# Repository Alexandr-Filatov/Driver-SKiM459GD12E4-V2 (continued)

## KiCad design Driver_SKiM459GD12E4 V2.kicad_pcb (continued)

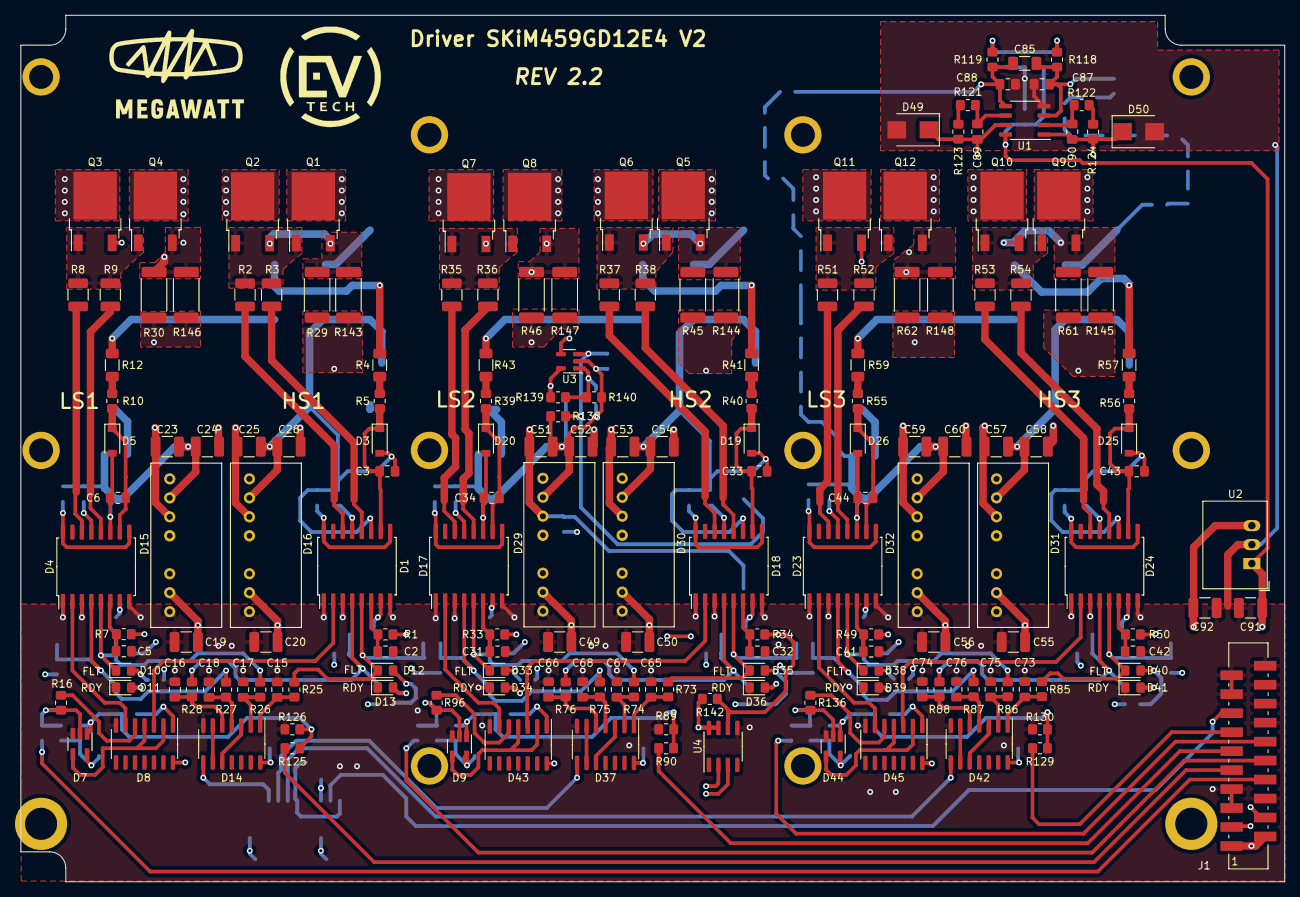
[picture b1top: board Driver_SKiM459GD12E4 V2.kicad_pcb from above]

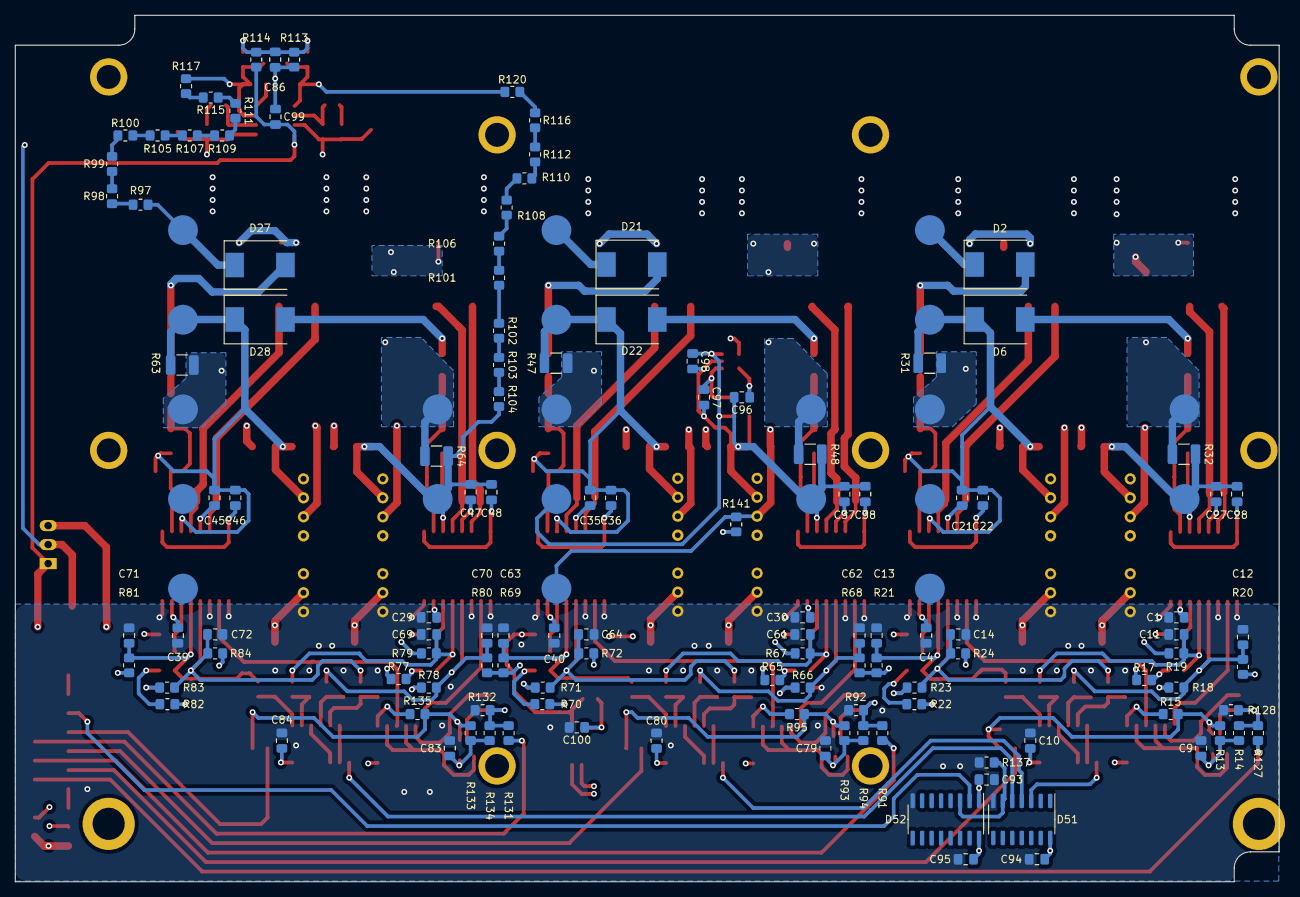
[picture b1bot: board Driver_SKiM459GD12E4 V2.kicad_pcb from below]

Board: 4 copper layers, 169.2 x 116.0 mm, 335 parts (143 on the bottom side), 184 nets.

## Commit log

2022-08-30 Прикидка
2022-11-21 Одна стойка
2022-11-25 Первая сырая расстановка, неполная
2022-11-26 Всё не вмещается
2022-11-28 Всё влезло, осталься компаратор на NTC
2022-12-12 Почти финальная версия
2022-12-12 Добавил сброс по температуре на все драйвера
2022-12-12 Исправмл логику защиты по температуре
2022-12-13 Добавил подтяжку к HCPL
2022-12-13 Добавил подтяжку на выход HCPL
2022-12-14 Добавил названия элементов в схеме
2023-02-16 Нашёл ошибки
2023-02-16 Исправил ошибки, добавил резисторы в затвор, ревизия 2.0
2023-03-21 REV2.1 - добавил конденсатор по питанию измерения DC
2023-03-27 Версия для резонита REV2.1
2023-03-27 Финальная версия для производства
2023-03-27 Отдал в резонит
2023-08-17 REV2.2 для резонита. Убрал переходные отверстия с контактных площадок и добавил логотип
